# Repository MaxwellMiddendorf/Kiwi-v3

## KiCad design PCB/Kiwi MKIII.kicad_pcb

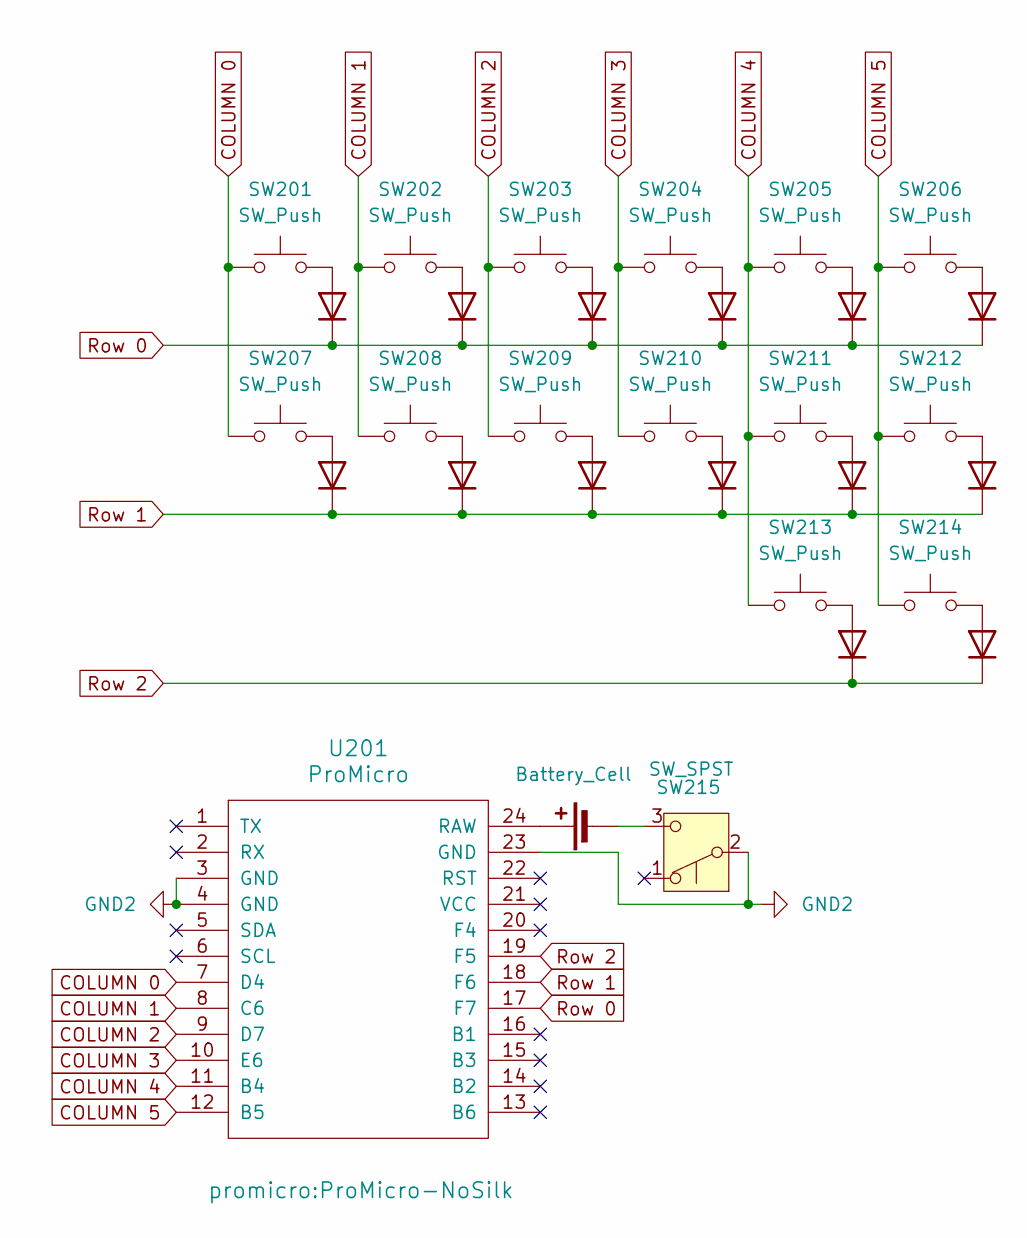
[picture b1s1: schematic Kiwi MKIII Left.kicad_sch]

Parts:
BT201: Battery_Cell; TestPoint_Bridge_Pitch5.08mm_Drill0.7mm
D201, D202, D203, D204, D205, D206, D207, D208, D209, D210, D211, D212, D213, D214: D; SOD3716X145N; Manufacturing Part 1N4148W-7-F; DigiKey 1N4148W-FDICT-ND
SW201, SW202, SW203, SW204, SW205, SW206, SW207, SW208, SW209, SW210, SW211, SW212, SW213, SW214: SW_Push; SW_Hotswap_Kailh_Choc_V1
SW215: SW_SPST; SW_SPDT_PCM12; Manufacturer Part MSK12C02; LCSC Part C431540
U201: ProMicro; ProMicro-NoSilk

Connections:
COLUMN 0: SW201.1, SW207.1, U201.7 (D4)
COLUMN 1: SW202.1, SW208.1, U201.8 (C6)
COLUMN 2: SW203.1, SW209.1, U201.9 (D7)
COLUMN 3: SW204.1, SW210.1, U201.10 (E6)
COLUMN 4: SW205.1, SW211.1, SW213.1, U201.11 (B4)
COLUMN 5: SW206.1, SW212.1, SW214.1, U201.12 (B5)
GND2: SW215.2 (B), U201.3 (GND), U201.4 (GND), U201.23 (GND)
unnamed: BT201.1 (+), U201.24 (RAW)
unnamed: BT201.2 (-), SW215.3 (C)
unnamed: D201.2 (A), SW201.2
unnamed: D202.2 (A), SW202.2
unnamed: D203.2 (A), SW203.2
unnamed: D204.2 (A), SW204.2
unnamed: D205.2 (A), SW205.2
unnamed: D206.2 (A), SW206.2
unnamed: D207.2 (A), SW207.2
unnamed: D208.2 (A), SW208.2
unnamed: D209.2 (A), SW209.2
unnamed: D210.2 (A), SW210.2
unnamed: D211.2 (A), SW211.2
unnamed: D212.2 (A), SW212.2
unnamed: D213.2 (A), SW213.2
unnamed: D214.2 (A), SW214.2
Row 0: D201.1 (K), D202.1 (K), D203.1 (K), D204.1 (K), D205.1 (K), D206.1 (K), U201.17 (F7)
Row 1: D207.1 (K), D208.1 (K), D209.1 (K), D210.1 (K), D211.1 (K), D212.1 (K), U201.18 (F6)
Row 2: D213.1 (K), D214.1 (K), U201.19 (F5)

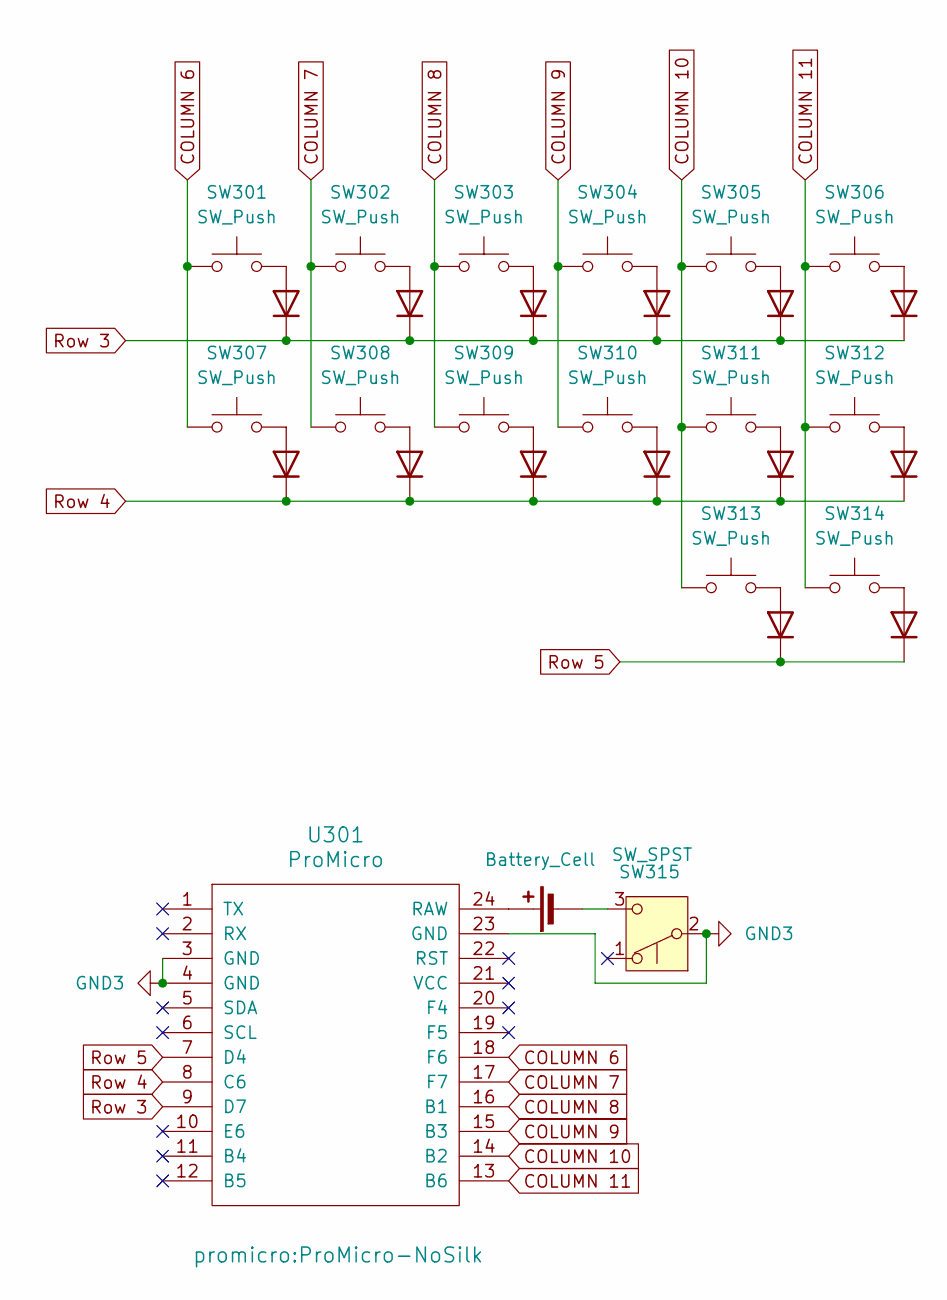
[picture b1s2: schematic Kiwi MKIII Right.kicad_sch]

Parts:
BT301: Battery_Cell; TestPoint_Bridge_Pitch5.08mm_Drill0.7mm
D301, D302, D303, D304, D305, D306, D307, D308, D309, D310, D311, D312, D313, D314: D; SOD3716X145N; Manufacturing Part 1N4148W-7-F; DigiKey 1N4148W-FDICT-ND
SW301, SW302, SW303, SW304, SW305, SW306, SW307, SW308, SW309, SW310, SW311, SW312, SW313, SW314: SW_Push; SW_Hotswap_Kailh_Choc_V1
SW315: SW_SPST; SW_SPDT_PCM12; Manufacturer Part MSK12C02; LCSC Part C431540
U301: ProMicro; ProMicro-NoSilk

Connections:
COLUMN 6: SW301.1, SW307.1, U301.18 (F6)
COLUMN 7: SW302.1, SW308.1, U301.17 (F7)
COLUMN 8: SW303.1, SW309.1, U301.16 (B1)
COLUMN 9: SW304.1, SW310.1, U301.15 (B3)
COLUMN 10: SW305.1, SW311.1, SW313.1, U301.14 (B2)
COLUMN 11: SW306.1, SW312.1, SW314.1, U301.13 (B6)
GND3: SW315.2 (B), U301.3 (GND), U301.4 (GND), U301.23 (GND)
unnamed: BT301.1 (+), U301.24 (RAW)
unnamed: BT301.2 (-), SW315.3 (C)
unnamed: D301.2 (A), SW301.2
unnamed: D302.2 (A), SW302.2
unnamed: D303.2 (A), SW303.2
unnamed: D304.2 (A), SW304.2
unnamed: D305.2 (A), SW305.2
unnamed: D306.2 (A), SW306.2
unnamed: D307.2 (A), SW307.2
unnamed: D308.2 (A), SW308.2
unnamed: D309.2 (A), SW309.2
unnamed: D310.2 (A), SW310.2
unnamed: D311.2 (A), SW311.2
unnamed: D312.2 (A), SW312.2
unnamed: D313.2 (A), SW313.2
unnamed: D314.2 (A), SW314.2
Row 3: D301.1 (K), D302.1 (K), D303.1 (K), D304.1 (K), D305.1 (K), D306.1 (K), U301.9 (D7)
Row 4: D307.1 (K), D308.1 (K), D309.1 (K), D310.1 (K), D311.1 (K), D312.1 (K), U301.8 (C6)
Row 5: D313.1 (K), D314.1 (K), U301.7 (D4)

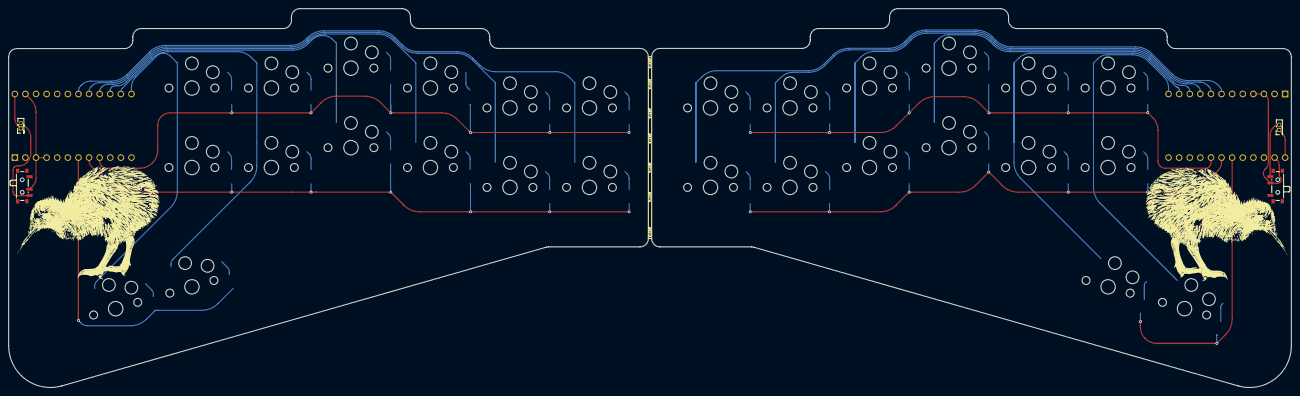
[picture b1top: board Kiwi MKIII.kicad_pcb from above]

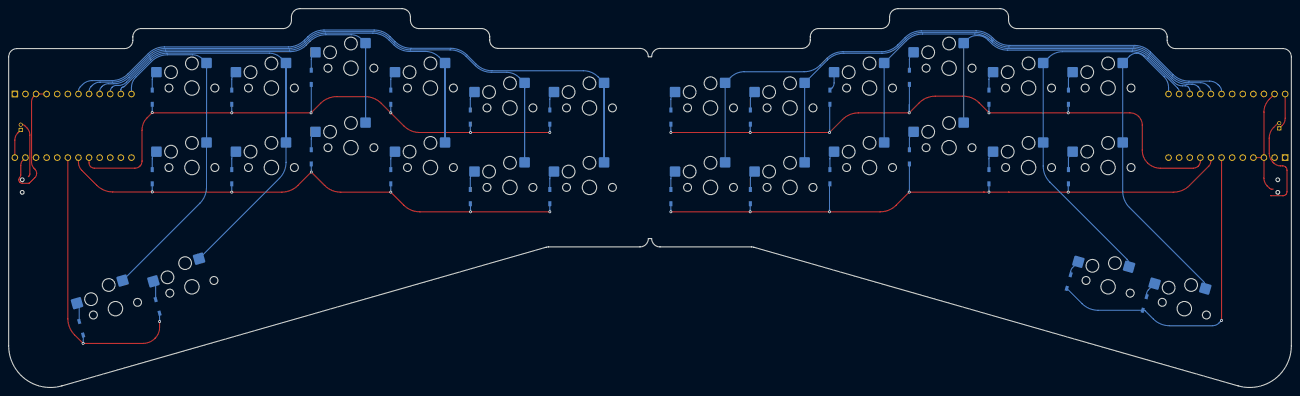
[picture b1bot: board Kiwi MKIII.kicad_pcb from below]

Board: 2 copper layers, 307.3 x 90.8 mm, 62 parts (28 on the bottom side), 52 nets.

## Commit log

2024-04-05 name change
2024-04-05 fixed directories
2024-04-05 updated shield configs
2024-04-05 add keymap
2024-04-05 added keymap
2024-04-05 moved keymap
2024-04-05 setup keymap
2024-04-05 added keymap to board
2024-04-05 fixed keymap rootnode issue
2024-04-05 fixed shaped of keymap
2024-04-05 fixed config names
2024-04-05 fixed strings
2024-04-05 Rename kconfig.shield to Kconfig.shield
2024-04-05 changed driver to matrix
2024-04-05 updated overlays
2024-04-05 fixed headers
2024-04-05 refixed headers
2024-04-05 fixed variable headers
2024-04-05 trying again
2024-04-05 again, again
2024-04-05 again x 3
2024-04-05 fixed col-off
2024-04-05 fixed pins
2024-04-05 keymap fixe maybe
2024-04-05 adjusted pins
2024-04-05 adjusted pins, better
2024-04-05 changed build parameters
2024-04-05 copied keymap
2024-04-05 clean keymap
2024-04-05 test keymap
2024-04-05 test keymap undo
2024-04-05 matched left with right
2024-04-05 keymap test again
2024-04-06 Fixed kiwi-v3.keymap Indentation
2024-04-07 fixed pin assignments
2024-04-07 changed left keys assignments
2024-04-07 fixed pin assignments labels
2024-04-07 fixed keymap numbers
2024-04-07 added settings reset build
2024-04-08 reorganized directory hierarchy
2024-04-08 fixed workflow
2024-04-08 organized hierarchy again
2024-04-08 reconfigured folders
2024-04-08 added circutry
2024-04-08 added circuitry
